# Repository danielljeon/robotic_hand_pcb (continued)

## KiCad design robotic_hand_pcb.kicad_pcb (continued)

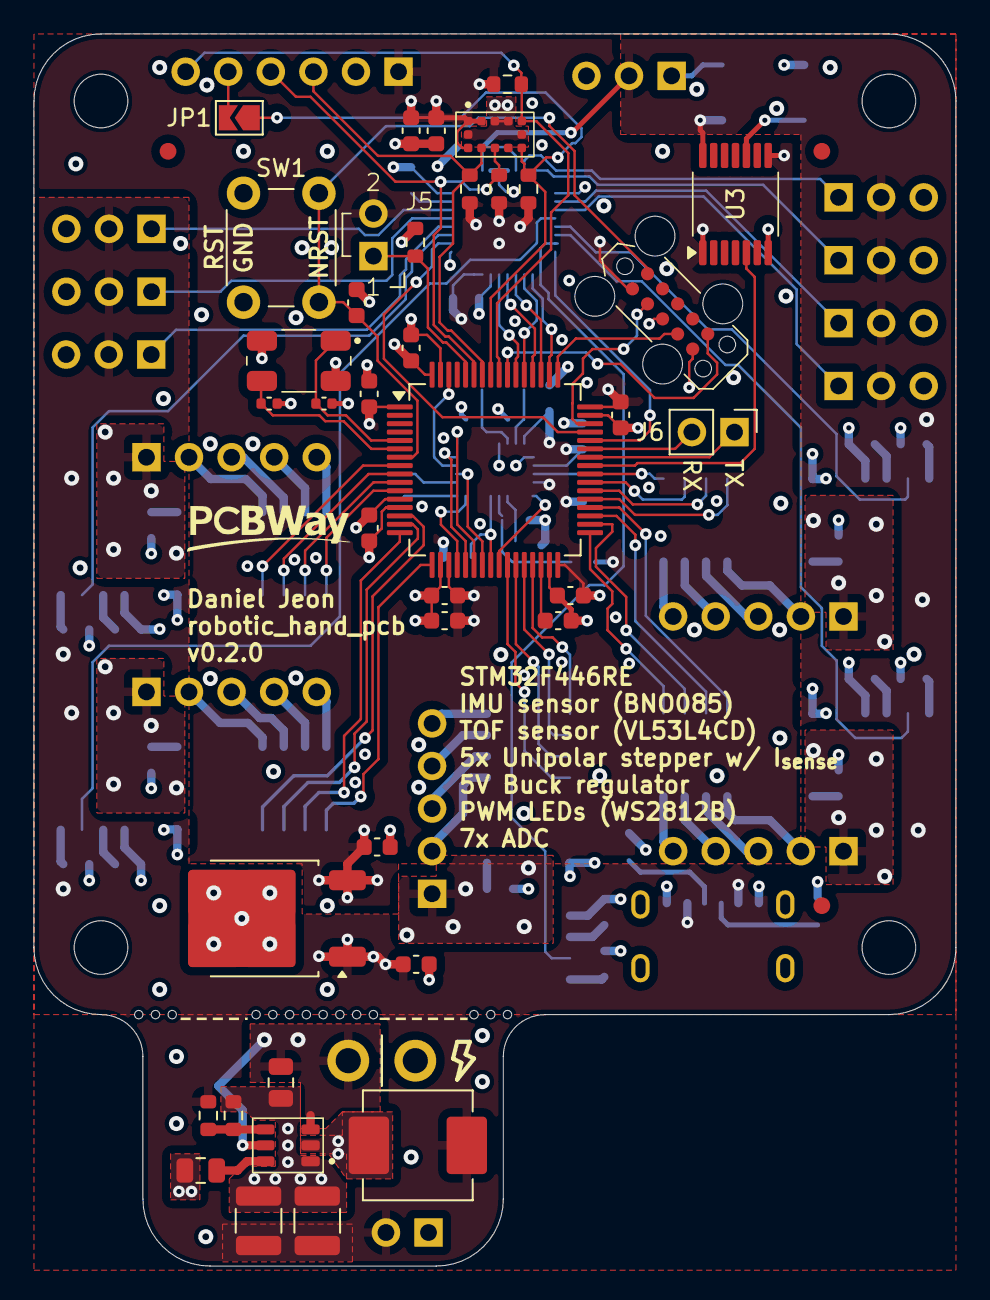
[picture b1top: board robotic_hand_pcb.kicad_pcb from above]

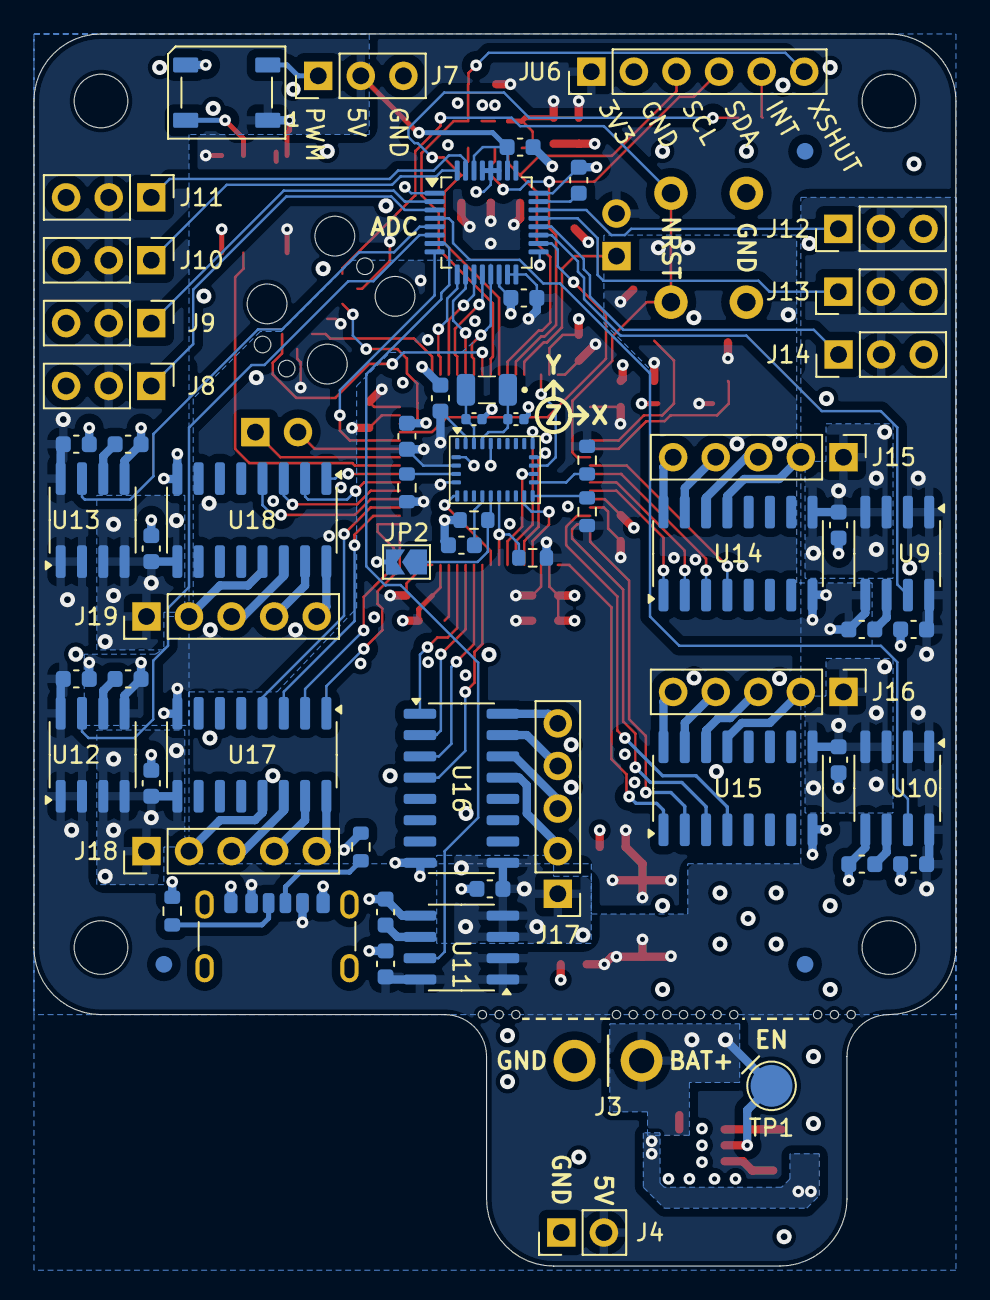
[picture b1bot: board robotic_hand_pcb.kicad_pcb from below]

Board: 4 copper layers, 55.0 x 73.5 mm, 111 parts (66 on the bottom side), 111 nets.

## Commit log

2025-01-28 Add gitignore and CODEOWNERS
2025-02-05 Begin recovery from branch nuke
2025-02-05 Add KiBot workflow files
2025-02-05 Recover WIP following branch nuke
2025-02-05 Add 5V buck regulator
2025-02-05 Pass ERC
2025-02-07 Update for WIP changes
2025-02-09 Update component_library
2025-02-09 Update symbol and footprint tables
2025-02-09 Add WIP schematic changes
2025-02-09 Pass ERC, update component_library
2025-02-09 Assign footprints
2025-02-09 Fix symbol error, update component_library
2025-02-09 Cleanup and remove unneeded connectors
2025-02-10 Add WIP PCB layout and routing
2025-02-11 Swap adafruit breakout for pin header footprint
2025-02-12 Update WIP, clean up stepper drivers
2025-02-13 Cleanup layout, add WIP routing
2025-02-13 Add minor layout improvements
2025-02-13 Route power, add major cleanup
2025-02-15 Near complete routing, cleanup
2025-02-15 Cleanup silkscreen
2025-02-17 Add WIP ADC routes
2025-02-18 Add WIP ADC and TOF routing
2025-02-19 Add initial WIP README.md docs
2025-02-21 Update README.md docs
2025-02-21 Fix borkd latex equations
2025-02-21 Add initial board spec tables
2025-02-21 Add WIP buck converter layout
2025-02-21 Initial full PCB design, pass DRC
2025-02-21 Fill empty spaces with GND pour
2025-02-21 Add stitching vias and final touches
2025-02-22 Cleanup and update docs
2025-02-22 Add README badge and update specs table
2025-02-22 Add PCBWay logo silkscreen
2025-02-22 Fix conflicting GPIO EXTI4 usage
2025-02-24 Add v0.1.0 release notes
2025-02-26 Fix C4 value error and cleanup silkscreen
2025-02-26 Update revision number
2025-03-02 Update simulation tool docs
2025-03-04 Fix README.md
2025-03-04 Add PSpice docs
2025-03-05 Add v0.1.0 assembly pictures
2025-03-17 Fix ADC IC decoupling
2025-03-17 Utilize AINCOM
2025-03-17 Add documentation related to issue #2
2025-03-19 Add test pad docs on README.md
2025-03-19 Fix test points README table column
2025-03-19 Add battery connector README docs
2025-03-24 Update README.md for v0.2.0 release
2025-10-18 Clean up picture docs
2025-10-18 Clean up picture docs (again)
